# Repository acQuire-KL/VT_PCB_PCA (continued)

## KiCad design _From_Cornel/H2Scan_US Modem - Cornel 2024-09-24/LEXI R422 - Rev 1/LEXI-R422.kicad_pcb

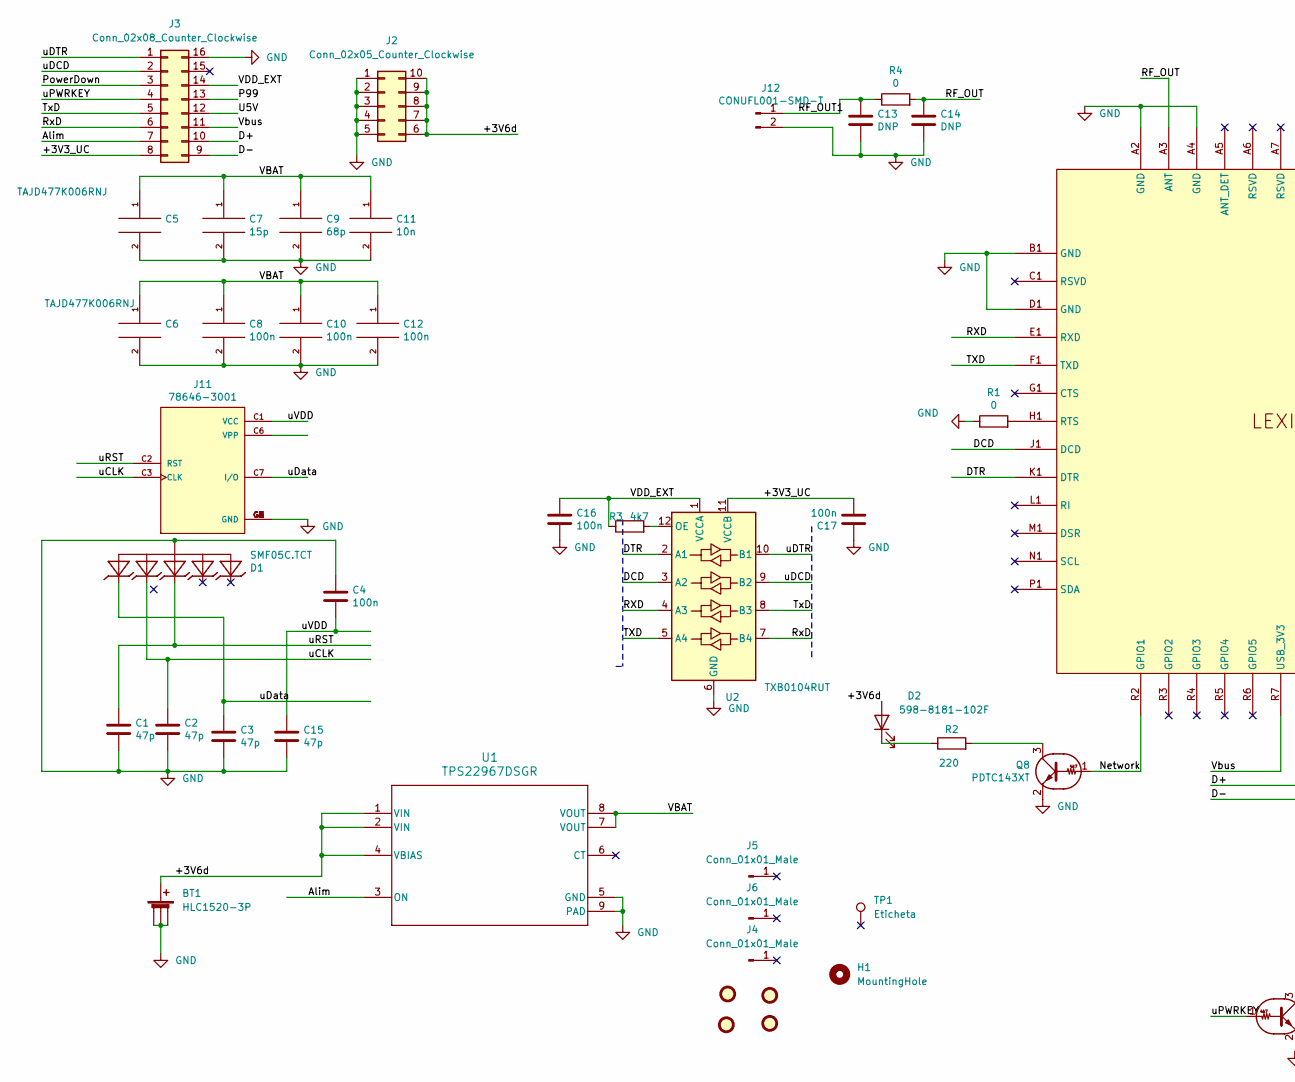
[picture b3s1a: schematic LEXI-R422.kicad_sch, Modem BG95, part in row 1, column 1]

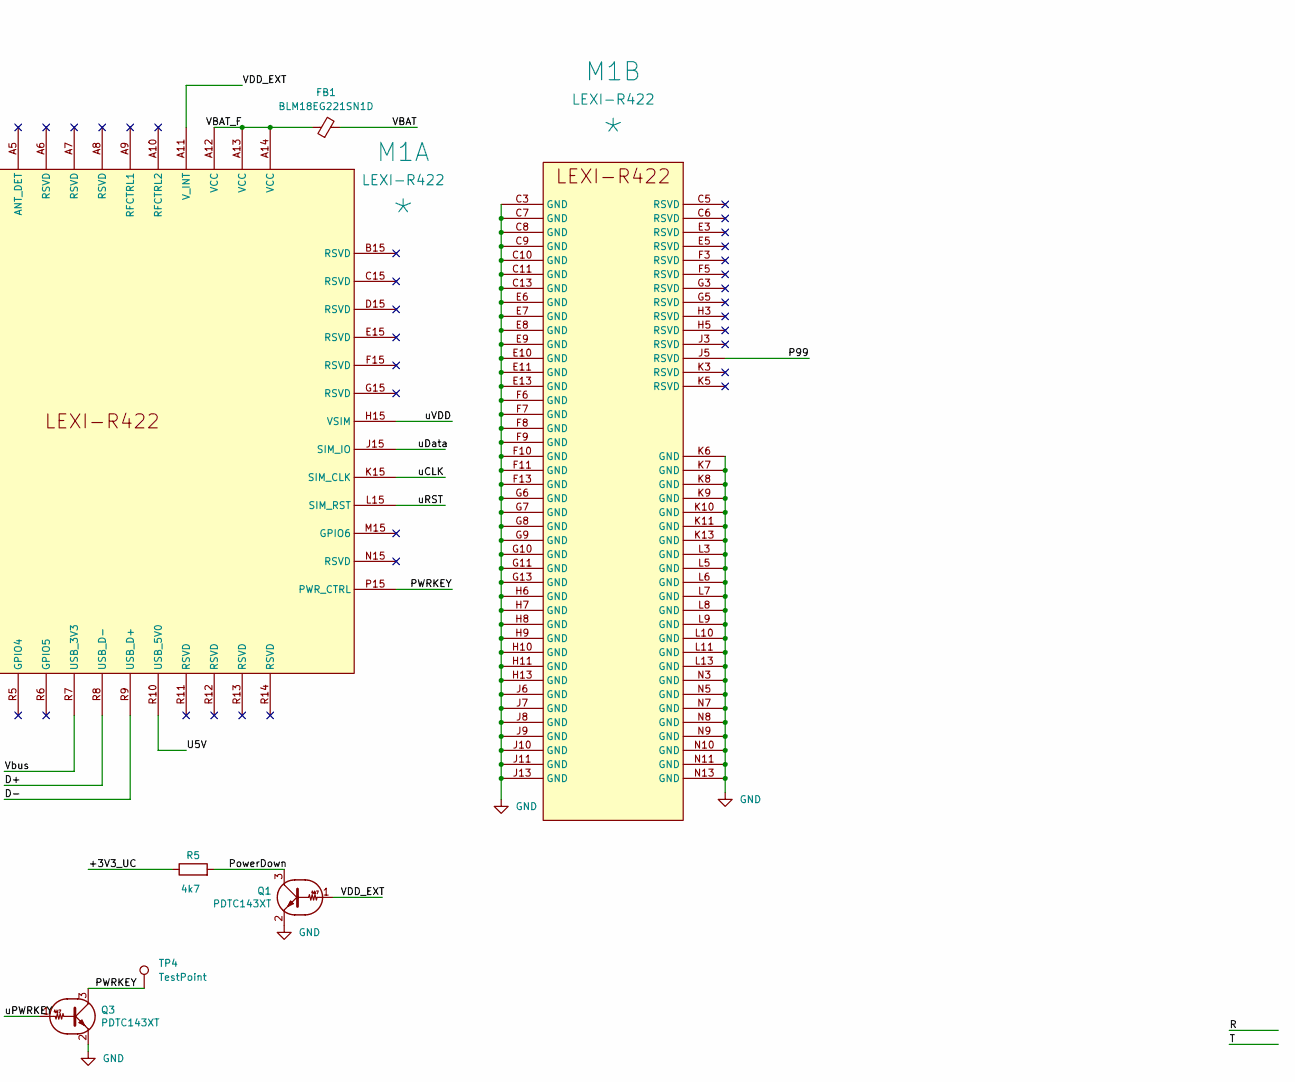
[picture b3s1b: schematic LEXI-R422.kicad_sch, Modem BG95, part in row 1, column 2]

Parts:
BT1: HLC1520-3P
C1, C2, C3, C15: 47p; C_0603_1608Metric
C4, C8, C10, C12, C16, C17: 100n; C_0603_1608Metric
C5, C6: TAJD477K006RNJ; CP_EIA-7361-38_AVX-V_Pad2.18x3.30mm_HandSolder
C7: 15p; C_0603_1608Metric
C9: 68p; C_0603_1608Metric
C11: 10n; C_0603_1608Metric
C13, C14: DNP; C_0603_1608Metric
D1: SMF05C.TCT; SC70-6
D2: 598-8181-102F; LED_0805_2012Metric
FB1: BLM18EG221SN1D; L_Walsin_WLFM201209x
FID1, FID2, FID3, FID4: Fiducial; Fiducial_1mm_Mask2mm
H1: MountingHole; MountingHole_2.5mm Simpla
J2: Conn_02x05_Counter_Clockwise; PinHeader_2x05_P2.54mm_Vertical_SMD_MOD
J3: Conn_02x08_Counter_Clockwise; PinHeader_2x08_P2.54mm_Vertical_SMD_MOD
J4, J5, J6: Conn_01x01_Male; TestPoint_Pad_5.1x5.1mm
J11: 78646-3001; MOLEX_78646-3001; DIGI-KEY_PART_NUMBER WM9364CT-ND
J12: CONUFL001-SMD-T; U.FL_Molex_MCRF_73412-0110_Vertical
M1: LEXI-R422; LEXI; Manufacturer P/N *
Q1, Q3, Q8: PDTC143XT; SOT-23
R1, R4: 0; R_0603_1608Metric
R2: 220; R_0603_1608Metric
R3, R5: 4k7; R_0603_1608Metric
TP1: Eticheta
TP4: TestPoint; TestPoint_Pad_D1.5mm
U1: TPS22967DSGR; WSON-8-1EP_2x2mm_P0.5mm_EP0.9x1.6mm_ThermalVias
U2: TXB0104RUT; Texas_R_PUQFN-N12

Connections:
/+3V3_UC: C17.2, J3.8, R5.1, U2.11 (VCCB)
/+3V6d: BT1.1 (+), D2.2 (A), J2.6, J2.7, J2.8, J2.9, J2.10, U1.1 (VIN), U1.2 (VIN), U1.4 (VBIAS)
/Alim: J3.7, U1.3 (ON)
/D+: J3.10, M1.R8 (USB_D-)
/D-: J3.9, M1.R9 (USB_D+)
/DCD: M1.J1 (DCD), U2.3 (A2)
/DTR: M1.K1 (DTR), U2.2 (A1)
/Network: M1.R2 (GPIO1), Q8.1 (B)
/P99: J3.13, M1.J5 (RSVD)
/PWRKEY: M1.P15 (PWR_CTRL), Q3.3 (C), TP4.1
/PowerDown: J3.3, Q1.3 (C), R5.2
/RF_OUT: C14.1, M1.A3 (ANT), R4.2
/RF_OUT1: C13.1, J12.1, R4.1
/RXD: M1.E1 (RXD), U2.4 (A3)
/RxD: J3.6, U2.7 (B4)
/TXD: M1.F1 (TXD), U2.5 (A4)
/TxD: J3.5, U2.8 (B3)
/U5V: J3.12, M1.R10 (USB_5V0)
/VBAT: C5.1, C6.1, C7.1, C8.1, C9.1, C10.1, C11.1, C12.1, FB1.2, U1.7 (VOUT), U1.8 (VOUT)
/VBAT_F: FB1.1, M1.A12 (VCC), M1.A13 (VCC), M1.A14 (VCC)
/VDD_EXT: C16.1, J3.14, M1.A11 (V_INT), Q1.1 (B), R3.1, U2.1 (VCCA)
/Vbus: J3.11, M1.R7 (USB_3V3)
/uCLK: C2.1, D1.5, J11.C3 (CLK), M1.K15 (SIM_CLK)
/uDCD: J3.2, U2.9 (B2)
/uDTR: J3.1, U2.10 (B1)
/uData: C3.1, D1.6, J11.C7 (I/O), M1.J15 (SIM_IO)
/uPWRKEY: J3.4, Q3.1 (B)
/uRST: C1.1, D1.4, J11.C2 (RST), M1.L15 (SIM_RST)
/uVDD: C4.2, C15.1, J11.C1 (VCC), M1.H15 (VSIM)
GND: BT1.2 (-), BT1.3 (-), BT1.4 (-), C1.2, C2.2, C3.2, C4.1, C5.2, C6.2, C7.2, C8.2, C9.2, C10.2, C11.2, C12.2, C13.2, C14.2, C15.2, C16.2, C17.1, D1.2, J2.1, J2.2, J2.3, J2.4, J2.5, J3.16, J11.C5 (GND), J11.G1 (GND), J11.G2 (GND), J11.G3 (GND), J11.G4 (GND), J11.G5 (GND), J11.G6 (GND), J12.2, M1.A2 (GND), M1.A4 (GND), M1.B1 (GND), M1.C3 (GND), M1.C7 (GND), M1.C8 (GND), M1.C9 (GND), M1.C10 (GND), M1.C11 (GND), M1.C13 (GND), M1.D1 (GND), M1.E6 (GND), M1.E7 (GND), M1.E8 (GND), M1.E9 (GND), M1.E10 (GND), M1.E11 (GND), M1.E13 (GND), M1.F6 (GND), M1.F7 (GND), M1.F8 (GND), M1.F9 (GND), M1.F10 (GND), M1.F11 (GND), M1.F13 (GND), M1.G6 (GND), M1.G7 (GND), M1.G8 (GND), M1.G9 (GND), M1.G10 (GND), M1.G11 (GND), M1.G13 (GND), M1.H6 (GND), M1.H7 (GND), M1.H8 (GND), M1.H9 (GND), M1.H10 (GND), M1.H11 (GND), M1.H13 (GND), M1.J6 (GND), M1.J7 (GND), M1.J8 (GND), M1.J9 (GND), M1.J10 (GND), M1.J11 (GND), M1.J13 (GND), M1.K6 (GND), M1.K7 (GND), M1.K8 (GND), M1.K9 (GND), M1.K10 (GND), M1.K11 (GND), M1.K13 (GND), M1.L3 (GND), M1.L5 (GND), M1.L6 (GND), M1.L7 (GND), M1.L8 (GND), M1.L9 (GND), M1.L10 (GND), M1.L11 (GND), M1.L13 (GND), M1.N3 (GND), M1.N5 (GND), M1.N7 (GND), M1.N8 (GND), M1.N9 (GND), M1.N10 (GND), M1.N11 (GND), M1.N13 (GND), Q1.2 (E), Q3.2 (E), Q8.2 (E), R1.1, U1.5 (GND), U1.9 (PAD), U2.6 (GND)
unnamed: D2.1 (K), R2.1
unnamed: M1.H1 (RTS), R1.2
unnamed: Q8.3 (C), R2.2
unnamed: R3.2, U2.12 (OE)

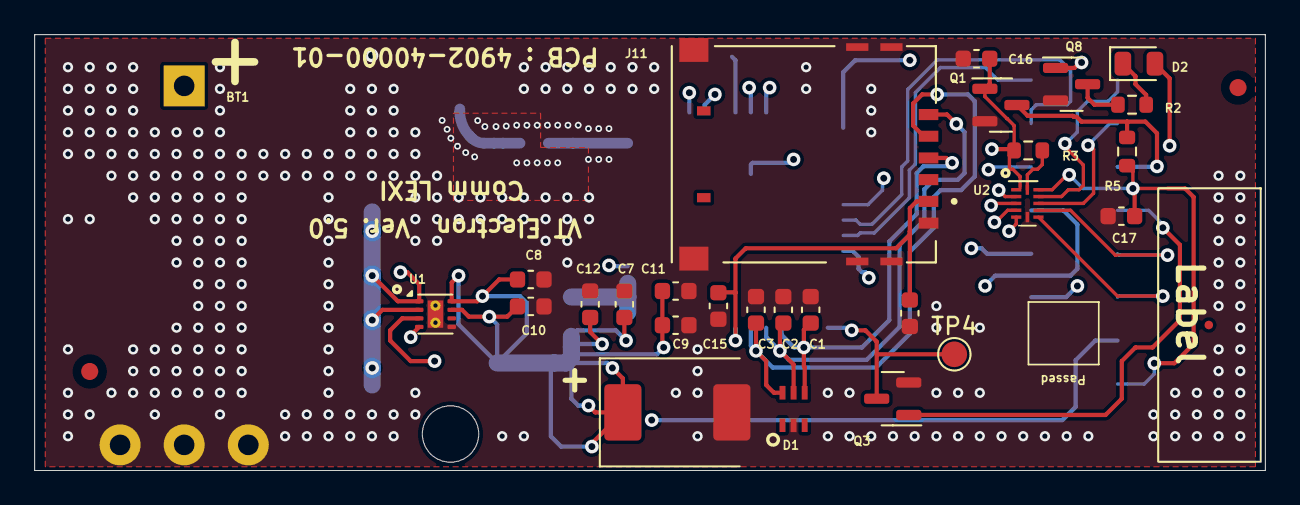
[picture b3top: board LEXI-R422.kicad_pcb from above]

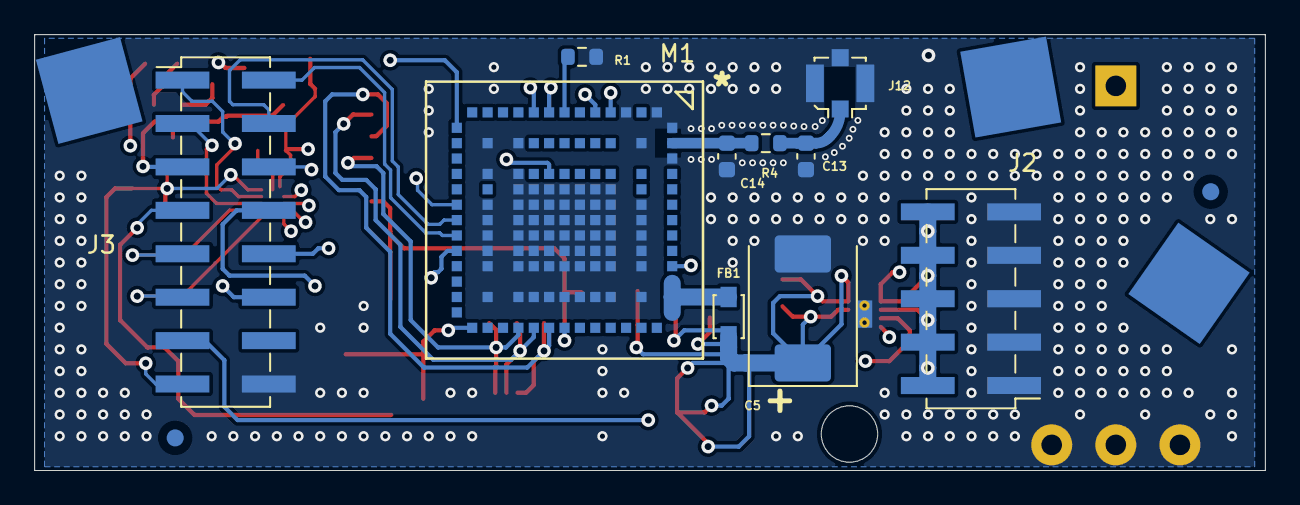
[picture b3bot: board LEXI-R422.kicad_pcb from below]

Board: 4 copper layers, 72.0 x 25.5 mm, 46 parts (15 on the bottom side), 34 nets.
